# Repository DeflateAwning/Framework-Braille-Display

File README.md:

# Framework-Braille-Display
A braille display for the Framework 13 laptop's touchpad, hopefully

## Project Status

⚠️ This project is still a work in progress. It is not usable, yet. ⚠️

If you are interested in helping design, test, or advise on this project, please reach out!

I'm not sure how long this project will take. The goal is to have a proof of concept by 2025-06-01.

## What is this?

This is a project to create a refreshable braille display, which is installable in the location of the Framework 13 laptop's touchpad.

A braille display is a device that allows blind and visually impaired people to read text on a computer screen by converting it to braille.

Manufacturing techniques, cost, etc. TBD.

## Why?

I am not blind. I am, however, disappointed in the lack of laptop-compatible braille displays, and the lack of affordable braille displays in general. I believe that an addition to the open source Framework laptop is a great way to make computers more accessible to visually impaired people from all countries.

### Braille Standards

* ISO 17049:2013 (Accessible design — Application of braille on signage, equipment and appliances)

| Parameter                                                | Min (mm) | Max (mm) | Nominal for Embossing (mm) |
|----------------------------------------------------------|----------|----------|----------------------------|
| Dot Base Diameter                                        | 1.5      | 1.6      | 1.44                       |
| Dot height                                               | 0.6      | 0.9      | 0.48                       |
| Dist. between two dots in the same cell                  | 2.3      | 2.5      | 2.34                       |
| Dist. between corresponding dots in cells (char-to-char) | 6.1      | 7.6      | 6.20                       |
| Dist. between corresponding dots in cells (row-to-row)   | 10.0     | 10.2     | 10.00                      |

### Framework Laptop
* CAD and electrical specs for the Framework 13 laptop: https://github.com/FrameworkComputer/Framework-Laptop-13

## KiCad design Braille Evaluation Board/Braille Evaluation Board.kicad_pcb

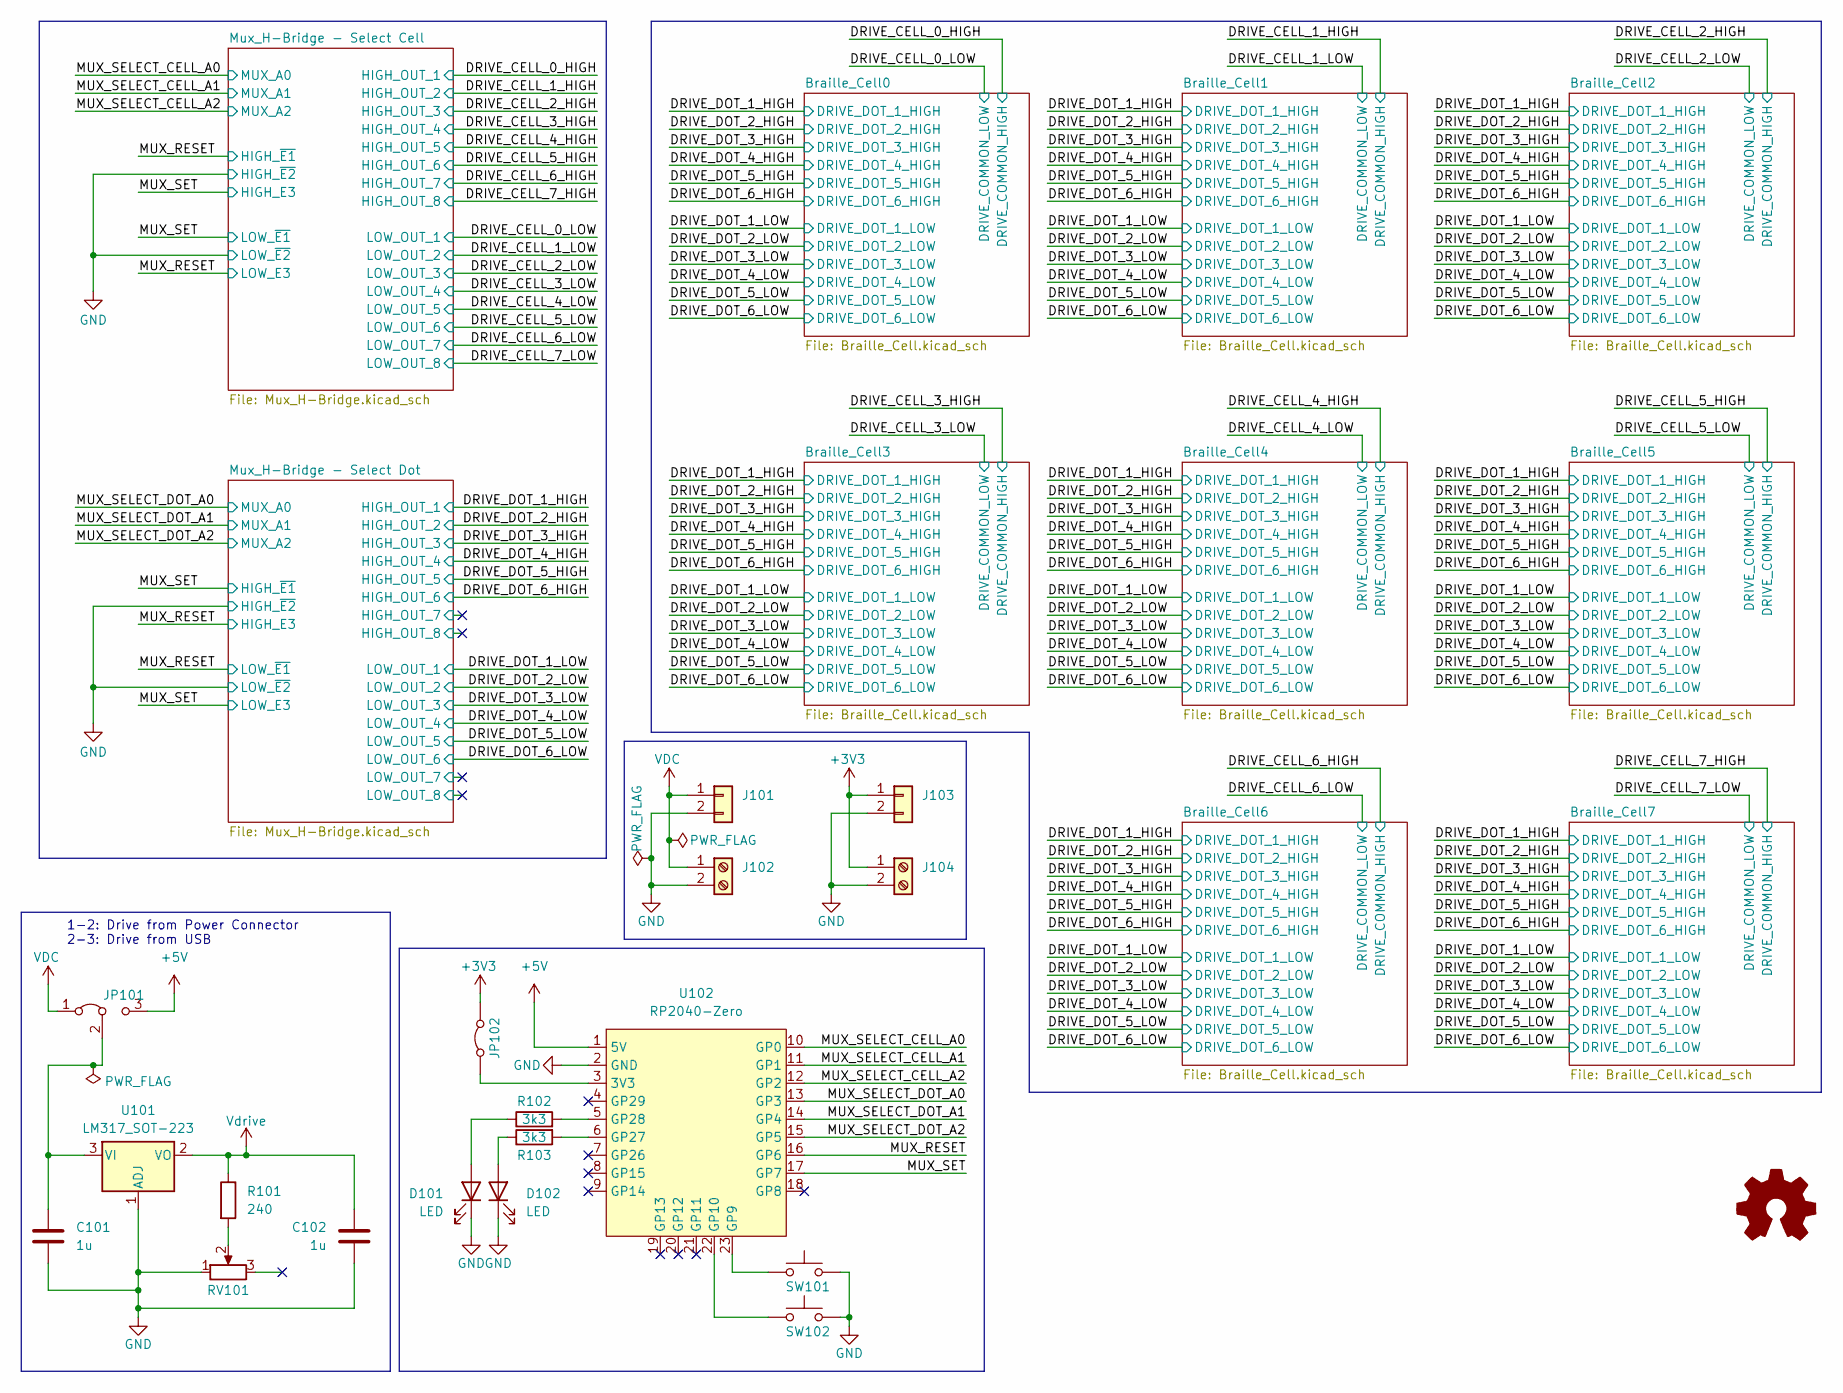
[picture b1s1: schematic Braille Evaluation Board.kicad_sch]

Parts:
C101, C102: 1u; C_1206_3216Metric_Pad1.33x1.80mm_HandSolder
D101, D102: LED; LED_1206_3216Metric_Pad1.42x1.75mm_HandSolder
J101, J103: Conn_01x02; PinHeader_1x02_P2.54mm_Vertical
J102, J104: Screw_Terminal_01x02; TerminalBlock_bornier-2_P5.08mm
JP101: Jumper_3_Bridged12; PinHeader_1x03_P2.54mm_Vertical
JP102: Jumper_2_Open; PinHeader_1x02_P2.54mm_Vertical
R101: 240; R_1206_3216Metric_Pad1.30x1.75mm_HandSolder
R102, R103: 3k3; R_1206_3216Metric_Pad1.30x1.75mm_HandSolder
RV101: R_Potentiometer; Potentiometer_Vishay_T73YP_Vertical
SW101, SW102: SW_Push; SW_PUSH_6mm_H5mm
U101: LM317_SOT-223; SOT-223-3_TabPin2
U102: RP2040-Zero; RP2040 Zero

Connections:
+3V3: J103.1, J104.1, JP102.2 (B); also elsewhere on the board
+5V: JP101.3 (B), U102.1 (5V)
/MUX_RESET: U102.16 (GP6); also elsewhere on the board
/MUX_SELECT_CELL_A0: U102.10 (GP0); also elsewhere on the board
/MUX_SELECT_CELL_A1: U102.11 (GP1); also elsewhere on the board
/MUX_SELECT_CELL_A2: U102.12 (GP2); also elsewhere on the board
/MUX_SELECT_DOT_A0: U102.13 (GP3); also elsewhere on the board
/MUX_SELECT_DOT_A1: U102.14 (GP4); also elsewhere on the board
/MUX_SELECT_DOT_A2: U102.15 (GP5); also elsewhere on the board
/MUX_SET: U102.17 (GP7); also elsewhere on the board
GND: C101.2, C102.2, D101.1 (K), D102.1 (K), J101.2, J102.2, J103.2, J104.2, RV101.1, SW101.2, SW102.2, U101.1 (ADJ), U102.2 (GND); also elsewhere on the board
unnamed: D101.2 (A), R102.1
unnamed: D102.2 (A), R103.1
unnamed: C101.1, JP101.2 (C), U101.3 (VI)
unnamed: JP102.1 (A), U102.3 (3V3)
unnamed: R101.2, RV101.2
unnamed: SW101.1, U102.23 (GP9)
unnamed: SW102.1, U102.22 (GP10)
unnamed: R103.2, U102.6 (GP27)
unnamed: R102.2, U102.5 (GP28)
VDC: J101.1, J102.1, JP101.1 (A)
Vdrive: C102.1, R101.1, U101.2 (VO); also elsewhere on the board

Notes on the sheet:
1-2: Drive from Power Connector 2-3: Drive from USB

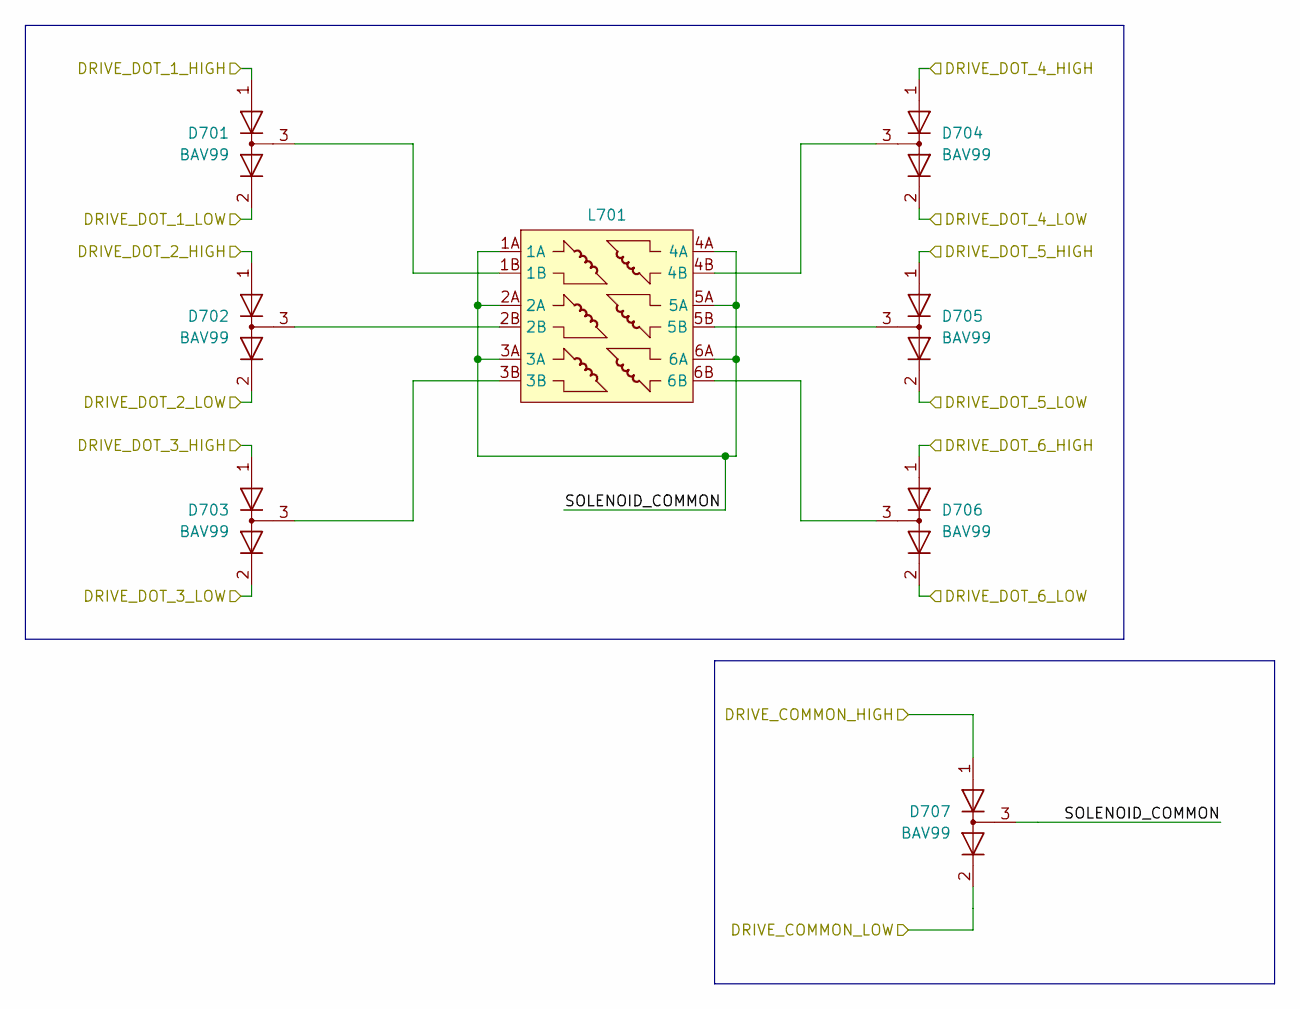
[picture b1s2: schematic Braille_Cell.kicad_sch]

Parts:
D701, D702, D703, D704, D705, D706, D707: BAV99; SOT-23_Handsoldering_EasyMode
L701: Solenoid_Braille_Cell

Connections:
/Braille_Cell3/SOLENOID_COMMON: D707.3 (K), L701.1A, L701.2A, L701.3A, L701.4A, L701.5A, L701.6A
/DRIVE_CELL_3_HIGH: D707.1 (K); also elsewhere on the board
/DRIVE_CELL_3_LOW: D707.2 (A); also elsewhere on the board
/DRIVE_DOT_1_HIGH: D701.1 (K); also elsewhere on the board
/DRIVE_DOT_1_LOW: D701.2 (A); also elsewhere on the board
/DRIVE_DOT_2_HIGH: D702.1 (K); also elsewhere on the board
/DRIVE_DOT_2_LOW: D702.2 (A); also elsewhere on the board
/DRIVE_DOT_3_HIGH: D703.1 (K); also elsewhere on the board
/DRIVE_DOT_3_LOW: D703.2 (A); also elsewhere on the board
/DRIVE_DOT_4_HIGH: D704.1 (K); also elsewhere on the board
/DRIVE_DOT_4_LOW: D704.2 (A); also elsewhere on the board
/DRIVE_DOT_5_HIGH: D705.1 (K); also elsewhere on the board
/DRIVE_DOT_5_LOW: D705.2 (A); also elsewhere on the board
/DRIVE_DOT_6_HIGH: D706.1 (K); also elsewhere on the board
/DRIVE_DOT_6_LOW: D706.2 (A); also elsewhere on the board
unnamed: D701.3 (K), L701.1B
unnamed: D702.3 (K), L701.2B
unnamed: D703.3 (K), L701.3B
unnamed: D704.3 (K), L701.4B
unnamed: D705.3 (K), L701.5B
unnamed: D706.3 (K), L701.6B

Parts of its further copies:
D401, D402, D403, D404, D405, D406, D407, D501, D502, D503, D504, D505, D506, D507, D601, D602, D603, D604, D605, D606, D607, D801, D802, D803, D804, D805, D806, D807, D901, D902, D903, D904, D905, D906, D907, D1001, D1002, D1003, D1004, D1005, D1006, D1007, D1101, D1102, D1103, D1104, D1105, D1106, D1107: BAV99; SOT-23_Handsoldering_EasyMode
L401, L501, L601, L801, L901, L1001, L1101: Solenoid_Braille_Cell

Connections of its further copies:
/Braille_Cell0/SOLENOID_COMMON: D407.3 (K), L401.1A, L401.2A, L401.3A, L401.4A, L401.5A, L401.6A
/Braille_Cell1/SOLENOID_COMMON: D507.3 (K), L501.1A, L501.2A, L501.3A, L501.4A, L501.5A, L501.6A
/Braille_Cell2/SOLENOID_COMMON: D607.3 (K), L601.1A, L601.2A, L601.3A, L601.4A, L601.5A, L601.6A
/Braille_Cell4/SOLENOID_COMMON: D807.3 (K), L801.1A, L801.2A, L801.3A, L801.4A, L801.5A, L801.6A
/Braille_Cell5/SOLENOID_COMMON: D907.3 (K), L901.1A, L901.2A, L901.3A, L901.4A, L901.5A, L901.6A
/Braille_Cell6/SOLENOID_COMMON: D1007.3 (K), L1001.1A, L1001.2A, L1001.3A, L1001.4A, L1001.5A, L1001.6A
/Braille_Cell7/SOLENOID_COMMON: D1107.3 (K), L1101.1A, L1101.2A, L1101.3A, L1101.4A, L1101.5A, L1101.6A
/DRIVE_CELL_0_HIGH: D407.1 (K); also elsewhere on the board
/DRIVE_CELL_0_LOW: D407.2 (A); also elsewhere on the board
/DRIVE_CELL_1_HIGH: D507.1 (K); also elsewhere on the board
/DRIVE_CELL_1_LOW: D507.2 (A); also elsewhere on the board
/DRIVE_CELL_2_HIGH: D607.1 (K); also elsewhere on the board
/DRIVE_CELL_2_LOW: D607.2 (A); also elsewhere on the board
/DRIVE_CELL_4_HIGH: D807.1 (K); also elsewhere on the board
/DRIVE_CELL_4_LOW: D807.2 (A); also elsewhere on the board
/DRIVE_CELL_5_HIGH: D907.1 (K); also elsewhere on the board
/DRIVE_CELL_5_LOW: D907.2 (A); also elsewhere on the board
/DRIVE_CELL_6_HIGH: D1007.1 (K); also elsewhere on the board
/DRIVE_CELL_6_LOW: D1007.2 (A); also elsewhere on the board
/DRIVE_CELL_7_HIGH: D1107.1 (K); also elsewhere on the board
/DRIVE_CELL_7_LOW: D1107.2 (A); also elsewhere on the board
/DRIVE_DOT_1_HIGH: D401.1 (K), D501.1 (K), D601.1 (K), D801.1 (K), D901.1 (K), D1001.1 (K), D1101.1 (K); also elsewhere on the board
/DRIVE_DOT_1_LOW: D401.2 (A), D501.2 (A), D601.2 (A), D801.2 (A), D901.2 (A), D1001.2 (A), D1101.2 (A); also elsewhere on the board
/DRIVE_DOT_2_HIGH: D402.1 (K), D502.1 (K), D602.1 (K), D802.1 (K), D902.1 (K), D1002.1 (K), D1102.1 (K); also elsewhere on the board
/DRIVE_DOT_2_LOW: D402.2 (A), D502.2 (A), D602.2 (A), D802.2 (A), D902.2 (A), D1002.2 (A), D1102.2 (A); also elsewhere on the board
/DRIVE_DOT_3_HIGH: D403.1 (K), D503.1 (K), D603.1 (K), D803.1 (K), D903.1 (K), D1003.1 (K), D1103.1 (K); also elsewhere on the board
/DRIVE_DOT_3_LOW: D403.2 (A), D503.2 (A), D603.2 (A), D803.2 (A), D903.2 (A), D1003.2 (A), D1103.2 (A); also elsewhere on the board
/DRIVE_DOT_4_HIGH: D404.1 (K), D504.1 (K), D604.1 (K), D804.1 (K), D904.1 (K), D1004.1 (K), D1104.1 (K); also elsewhere on the board
/DRIVE_DOT_4_LOW: D404.2 (A), D504.2 (A), D604.2 (A), D804.2 (A), D904.2 (A), D1004.2 (A), D1104.2 (A); also elsewhere on the board
/DRIVE_DOT_5_HIGH: D405.1 (K), D505.1 (K), D605.1 (K), D805.1 (K), D905.1 (K), D1005.1 (K), D1105.1 (K); also elsewhere on the board
/DRIVE_DOT_5_LOW: D405.2 (A), D505.2 (A), D605.2 (A), D805.2 (A), D905.2 (A), D1005.2 (A), D1105.2 (A); also elsewhere on the board
/DRIVE_DOT_6_HIGH: D406.1 (K), D506.1 (K), D606.1 (K), D806.1 (K), D906.1 (K), D1006.1 (K), D1106.1 (K); also elsewhere on the board
/DRIVE_DOT_6_LOW: D406.2 (A), D506.2 (A), D606.2 (A), D806.2 (A), D906.2 (A), D1006.2 (A), D1106.2 (A); also elsewhere on the board
unnamed: D401.3 (K), L401.1B
unnamed: D402.3 (K), L401.2B
unnamed: D403.3 (K), L401.3B
unnamed: D404.3 (K), L401.4B
unnamed: D405.3 (K), L401.5B
unnamed: D406.3 (K), L401.6B
unnamed: D501.3 (K), L501.1B
unnamed: D502.3 (K), L501.2B
unnamed: D503.3 (K), L501.3B
unnamed: D504.3 (K), L501.4B
unnamed: D505.3 (K), L501.5B
unnamed: D506.3 (K), L501.6B
unnamed: D601.3 (K), L601.1B
unnamed: D602.3 (K), L601.2B
unnamed: D603.3 (K), L601.3B
unnamed: D604.3 (K), L601.4B
unnamed: D605.3 (K), L601.5B
unnamed: D606.3 (K), L601.6B
unnamed: D801.3 (K), L801.1B
unnamed: D802.3 (K), L801.2B
unnamed: D803.3 (K), L801.3B
unnamed: D804.3 (K), L801.4B
unnamed: D805.3 (K), L801.5B
unnamed: D806.3 (K), L801.6B
unnamed: D901.3 (K), L901.1B
unnamed: D902.3 (K), L901.2B
unnamed: D903.3 (K), L901.3B
unnamed: D904.3 (K), L901.4B
unnamed: D905.3 (K), L901.5B
unnamed: D906.3 (K), L901.6B
unnamed: D1001.3 (K), L1001.1B
unnamed: D1002.3 (K), L1001.2B
unnamed: D1003.3 (K), L1001.3B
unnamed: D1004.3 (K), L1001.4B
unnamed: D1005.3 (K), L1001.5B
unnamed: D1006.3 (K), L1001.6B
unnamed: D1101.3 (K), L1101.1B
unnamed: D1102.3 (K), L1101.2B
unnamed: D1103.3 (K), L1101.3B
unnamed: D1104.3 (K), L1101.4B
unnamed: D1105.3 (K), L1101.5B
unnamed: D1106.3 (K), L1101.6B

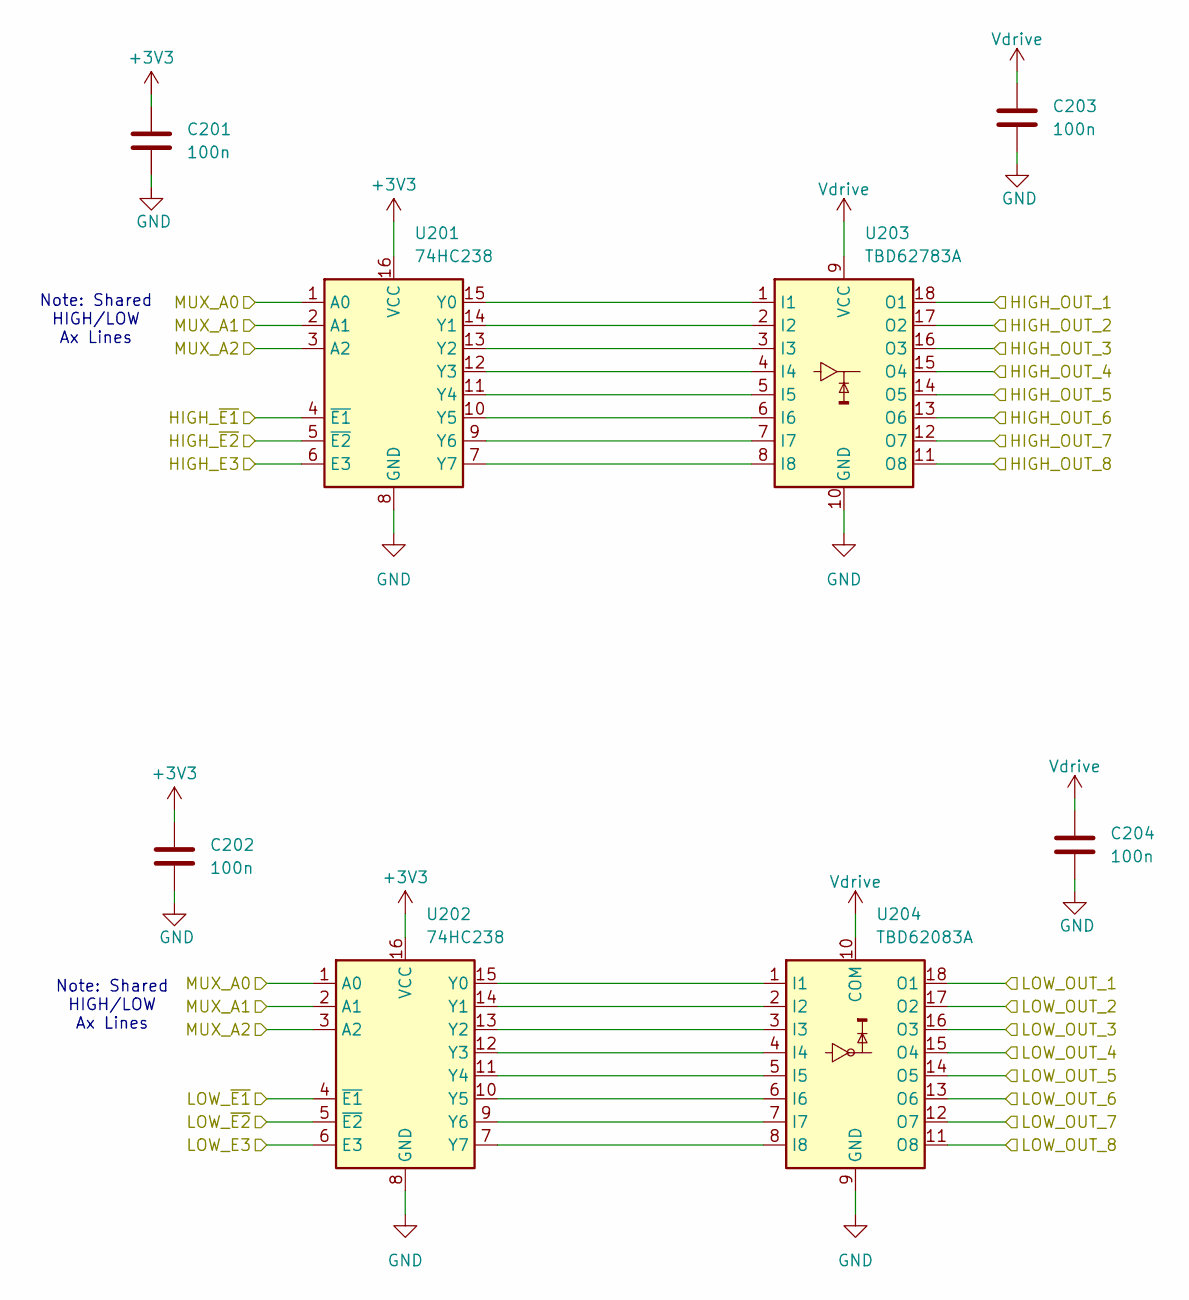
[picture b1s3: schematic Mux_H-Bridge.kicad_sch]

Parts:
C201, C202, C203, C204: 100n; C_1206_3216Metric_Pad1.33x1.80mm_HandSolder
U201, U202: 74HC238; SOIC-16_3.9x9.9mm_P1.27mm
U203: TBD62783A; SOIC-18W_7.5x11.6mm_P1.27mm
U204: TBD62083A; SOIC-18W_7.5x11.6mm_P1.27mm

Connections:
+3V3: C201.1, C202.1, U201.16 (VCC), U202.16 (VCC); also elsewhere on the board
/DRIVE_CELL_0_HIGH: U203.18 (O1); also elsewhere on the board
/DRIVE_CELL_0_LOW: U204.18 (O1); also elsewhere on the board
/DRIVE_CELL_1_HIGH: U203.17 (O2); also elsewhere on the board
/DRIVE_CELL_1_LOW: U204.17 (O2); also elsewhere on the board
/DRIVE_CELL_2_HIGH: U203.16 (O3); also elsewhere on the board
/DRIVE_CELL_2_LOW: U204.16 (O3); also elsewhere on the board
/DRIVE_CELL_3_HIGH: U203.15 (O4); also elsewhere on the board
/DRIVE_CELL_3_LOW: U204.15 (O4); also elsewhere on the board
/DRIVE_CELL_4_HIGH: U203.14 (O5); also elsewhere on the board
/DRIVE_CELL_4_LOW: U204.14 (O5); also elsewhere on the board
/DRIVE_CELL_5_HIGH: U203.13 (O6); also elsewhere on the board
/DRIVE_CELL_5_LOW: U204.13 (O6); also elsewhere on the board
/DRIVE_CELL_6_HIGH: U203.12 (O7); also elsewhere on the board
/DRIVE_CELL_6_LOW: U204.12 (O7); also elsewhere on the board
/DRIVE_CELL_7_HIGH: U203.11 (O8); also elsewhere on the board
/DRIVE_CELL_7_LOW: U204.11 (O8); also elsewhere on the board
/MUX_RESET: U201.4 (~E1), U202.6 (E3); also elsewhere on the board
/MUX_SELECT_CELL_A0: U201.1 (A0), U202.1 (A0); also elsewhere on the board
/MUX_SELECT_CELL_A1: U201.2 (A1), U202.2 (A1); also elsewhere on the board
/MUX_SELECT_CELL_A2: U201.3 (A2), U202.3 (A2); also elsewhere on the board
/MUX_SET: U201.6 (E3), U202.4 (~E1); also elsewhere on the board
GND: C201.2, C202.2, C203.2, C204.2, U201.5 (~E2), U201.8 (GND), U202.5 (~E2), U202.8 (GND), U203.10 (GND), U204.9 (GND); also elsewhere on the board
unnamed: U201.15 (Y0), U203.1 (I1)
unnamed: U201.14 (Y1), U203.2 (I2)
unnamed: U201.13 (Y2), U203.3 (I3)
unnamed: U201.12 (Y3), U203.4 (I4)
unnamed: U201.11 (Y4), U203.5 (I5)
unnamed: U201.10 (Y5), U203.6 (I6)
unnamed: U201.9 (Y6), U203.7 (I7)
unnamed: U201.7 (Y7), U203.8 (I8)
unnamed: U202.15 (Y0), U204.1 (I1)
unnamed: U202.14 (Y1), U204.2 (I2)
unnamed: U202.13 (Y2), U204.3 (I3)
unnamed: U202.12 (Y3), U204.4 (I4)
unnamed: U202.11 (Y4), U204.5 (I5)
unnamed: U202.10 (Y5), U204.6 (I6)
unnamed: U202.9 (Y6), U204.7 (I7)
unnamed: U202.7 (Y7), U204.8 (I8)
Vdrive: C203.1, C204.1, U203.9 (VCC), U204.10 (COM); also elsewhere on the board

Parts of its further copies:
C301, C302, C303, C304: 100n; C_1206_3216Metric_Pad1.33x1.80mm_HandSolder
U301, U302: 74HC238; SOIC-16_3.9x9.9mm_P1.27mm
U303: TBD62783A; SOIC-18W_7.5x11.6mm_P1.27mm
U304: TBD62083A; SOIC-18W_7.5x11.6mm_P1.27mm

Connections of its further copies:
+3V3: C301.1, C302.1, U301.16 (VCC), U302.16 (VCC); also elsewhere on the board
/DRIVE_DOT_1_HIGH: U303.18 (O1); also elsewhere on the board
/DRIVE_DOT_1_LOW: U304.18 (O1); also elsewhere on the board
/DRIVE_DOT_2_HIGH: U303.17 (O2); also elsewhere on the board
/DRIVE_DOT_2_LOW: U304.17 (O2); also elsewhere on the board
/DRIVE_DOT_3_HIGH: U303.16 (O3); also elsewhere on the board
/DRIVE_DOT_3_LOW: U304.16 (O3); also elsewhere on the board
/DRIVE_DOT_4_HIGH: U303.15 (O4); also elsewhere on the board
/DRIVE_DOT_4_LOW: U304.15 (O4); also elsewhere on the board
/DRIVE_DOT_5_HIGH: U303.14 (O5); also elsewhere on the board
/DRIVE_DOT_5_LOW: U304.14 (O5); also elsewhere on the board
/DRIVE_DOT_6_HIGH: U303.13 (O6); also elsewhere on the board
/DRIVE_DOT_6_LOW: U304.13 (O6); also elsewhere on the board
/MUX_RESET: U301.6 (E3), U302.4 (~E1); also elsewhere on the board
/MUX_SELECT_DOT_A0: U301.1 (A0), U302.1 (A0); also elsewhere on the board
/MUX_SELECT_DOT_A1: U301.2 (A1), U302.2 (A1); also elsewhere on the board
/MUX_SELECT_DOT_A2: U301.3 (A2), U302.3 (A2); also elsewhere on the board
/MUX_SET: U301.4 (~E1), U302.6 (E3); also elsewhere on the board
/Mux_H-Bridge - Select Dot/HIGH_OUT_7: U303.12 (O7)
/Mux_H-Bridge - Select Dot/HIGH_OUT_8: U303.11 (O8)
/Mux_H-Bridge - Select Dot/LOW_OUT_7: U304.12 (O7)
/Mux_H-Bridge - Select Dot/LOW_OUT_8: U304.11 (O8)
GND: C301.2, C302.2, C303.2, C304.2, U301.5 (~E2), U301.8 (GND), U302.5 (~E2), U302.8 (GND), U303.10 (GND), U304.9 (GND); also elsewhere on the board
unnamed: U301.15 (Y0), U303.1 (I1)
unnamed: U301.14 (Y1), U303.2 (I2)
unnamed: U301.13 (Y2), U303.3 (I3)
unnamed: U301.12 (Y3), U303.4 (I4)
unnamed: U301.11 (Y4), U303.5 (I5)
unnamed: U301.10 (Y5), U303.6 (I6)
unnamed: U301.9 (Y6), U303.7 (I7)
unnamed: U301.7 (Y7), U303.8 (I8)
unnamed: U302.15 (Y0), U304.1 (I1)
unnamed: U302.14 (Y1), U304.2 (I2)
unnamed: U302.13 (Y2), U304.3 (I3)
unnamed: U302.12 (Y3), U304.4 (I4)
unnamed: U302.11 (Y4), U304.5 (I5)
unnamed: U302.10 (Y5), U304.6 (I6)
unnamed: U302.9 (Y6), U304.7 (I7)
unnamed: U302.7 (Y7), U304.8 (I8)
Vdrive: C303.1, C304.1, U303.9 (VCC), U304.10 (COM); also elsewhere on the board

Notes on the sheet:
Note: Shared HIGH/LOW Ax Lines

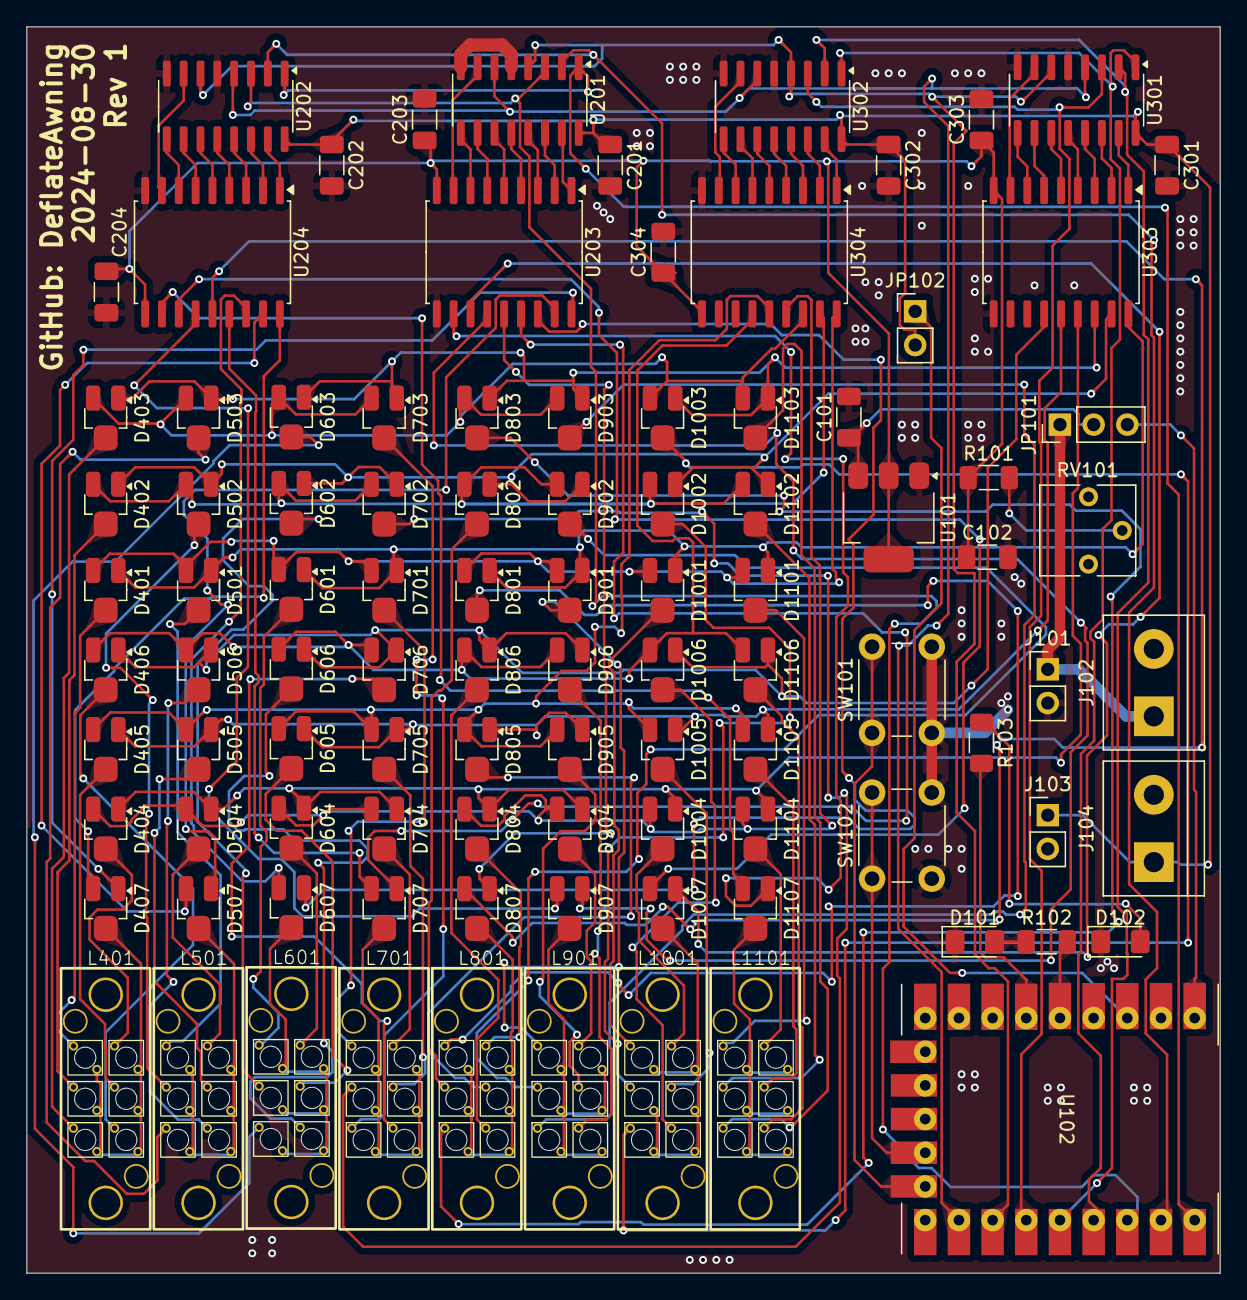
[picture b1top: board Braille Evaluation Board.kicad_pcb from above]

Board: 2 copper layers, 90.0 x 94.0 mm, 98 parts (0 on the bottom side), 138 nets.

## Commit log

2024-08-19 Add license
2024-08-19 Add project info to README
2024-08-19 Add more references and research
2024-08-23 Add dimensional specification
2024-08-31 Create PCB design
2024-08-31 Create Rev 1
2024-09-20 Clean up README
2024-09-20 Create cell mask pattern render
2024-09-20 Rename mask calculator
2024-09-20 Create `braille_cell_mask_pattern/braille_cell_mask_pattern_per_cell.py` script
